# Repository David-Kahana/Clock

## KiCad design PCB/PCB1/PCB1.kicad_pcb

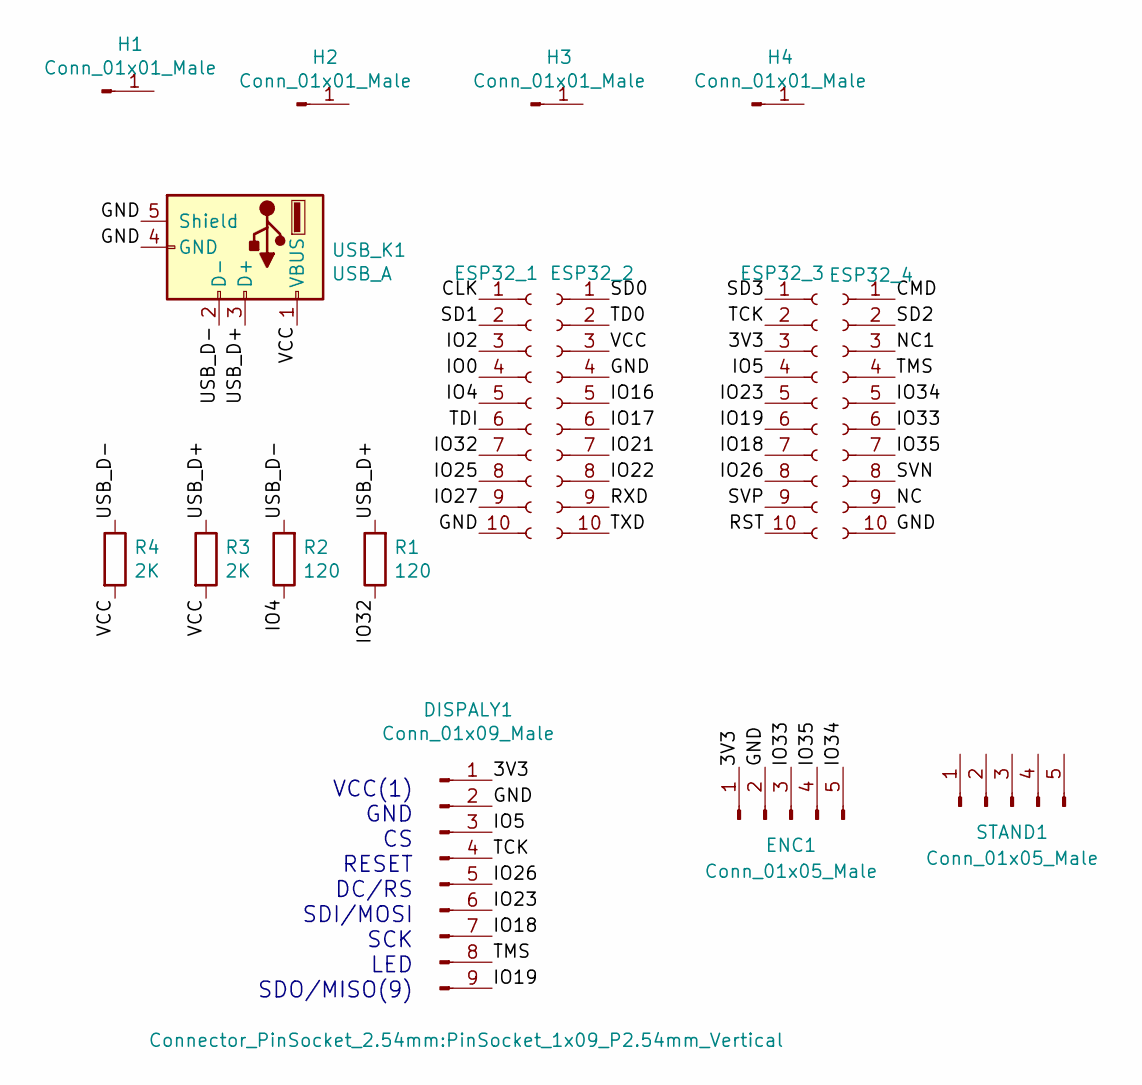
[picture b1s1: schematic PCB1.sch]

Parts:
DISPALY1: Conn_01x09_Male; PinSocket_1x09_P2.54mm_Vertical
ENC1: Conn_01x05_Male; PinSocket_1x05_P2.54mm_Vertical
ESP32_1, ESP32_2, ESP32_3, ESP32_4: Conn_01x10_Female; PinSocket_1x10_P2.54mm_Vertical
H1, H2, H3, H4: Conn_01x01_Male; SolderWirePad_1x01_Drill2mm
R1, R2: 120; R_0805_2012Metric
R3, R4: 2K; R_0805_2012Metric
STAND1: Conn_01x05_Male; PinSocket_1x05_P2.54mm_Vertical
USB_K1: USB_A; USB_A_Stewart_SS-52100-001_Horizontal

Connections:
/3V3: DISPALY1.1, ENC1.1, ESP32_3.3
/CLK: ESP32_1.1
/CMD: ESP32_4.1
/GND: DISPALY1.2, ENC1.2, ESP32_1.10, ESP32_2.4, ESP32_4.10, USB_K1.4 (GND), USB_K1.5 (Shield)
/IO0: ESP32_1.4
/IO2: ESP32_1.3
/IO4: ESP32_1.5, R2.1
/IO5: DISPALY1.3, ESP32_3.4
/IO16: ESP32_2.5
/IO17: ESP32_2.6
/IO18: DISPALY1.7, ESP32_3.7
/IO19: DISPALY1.9, ESP32_3.6
/IO21: ESP32_2.7
/IO22: ESP32_2.8
/IO23: DISPALY1.6, ESP32_3.5
/IO25: ESP32_1.8
/IO26: DISPALY1.5, ESP32_3.8
/IO27: ESP32_1.9
/IO32: ESP32_1.7, R1.1
/IO33: ENC1.3, ESP32_4.6
/IO34: ENC1.5, ESP32_4.5
/IO35: ENC1.4, ESP32_4.7
/NC: ESP32_4.9
/NC1: ESP32_4.3
/RST: ESP32_3.10
/RXD: ESP32_2.9
/SD0: ESP32_2.1
/SD1: ESP32_1.2
/SD2: ESP32_4.2
/SD3: ESP32_3.1
/SVN: ESP32_4.8
/SVP: ESP32_3.9
/TCK: DISPALY1.4, ESP32_3.2
/TD0: ESP32_2.2
/TDI: ESP32_1.6
/TMS: DISPALY1.8, ESP32_4.4
/TXD: ESP32_2.10
/USB_D+: R1.2, R3.1, USB_K1.3 (D+)
/USB_D-: R2.2, R4.1, USB_K1.2 (D-)
/VCC: ESP32_2.3, R3.2, R4.2, USB_K1.1 (VBUS)

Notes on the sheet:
VCC(1) GND CS RESET DC/RS SDI/MOSI SCK LED SDO/MISO(9)

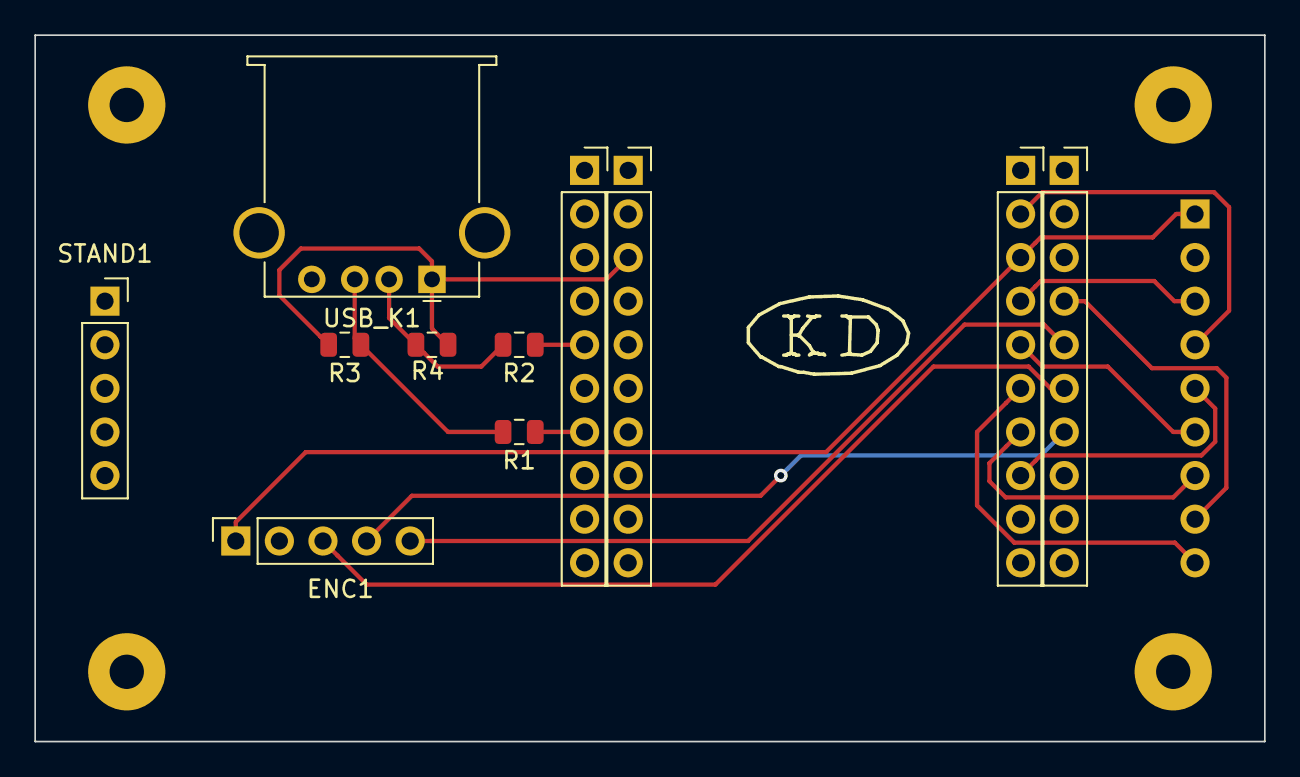
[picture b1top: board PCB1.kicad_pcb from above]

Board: 2 copper layers, 71.6 x 41.1 mm, 16 parts (1 on the bottom side), 17 nets.

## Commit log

2020-05-14 first
2020-05-14 Added PCB
2020-05-14 Added wifiWrapper
2020-05-14 less flicker
2020-05-14 highlight and scroll works
2020-05-15 Moved code to MyClock class
2020-05-29 adde knob
2023-11-05 for esp32s3
2023-11-05 internal FFat by async web server
2023-11-05 cleanup and seperating code
2023-11-05 cleanup and seperating code 2
2023-11-10 cleaning gfx stuff
